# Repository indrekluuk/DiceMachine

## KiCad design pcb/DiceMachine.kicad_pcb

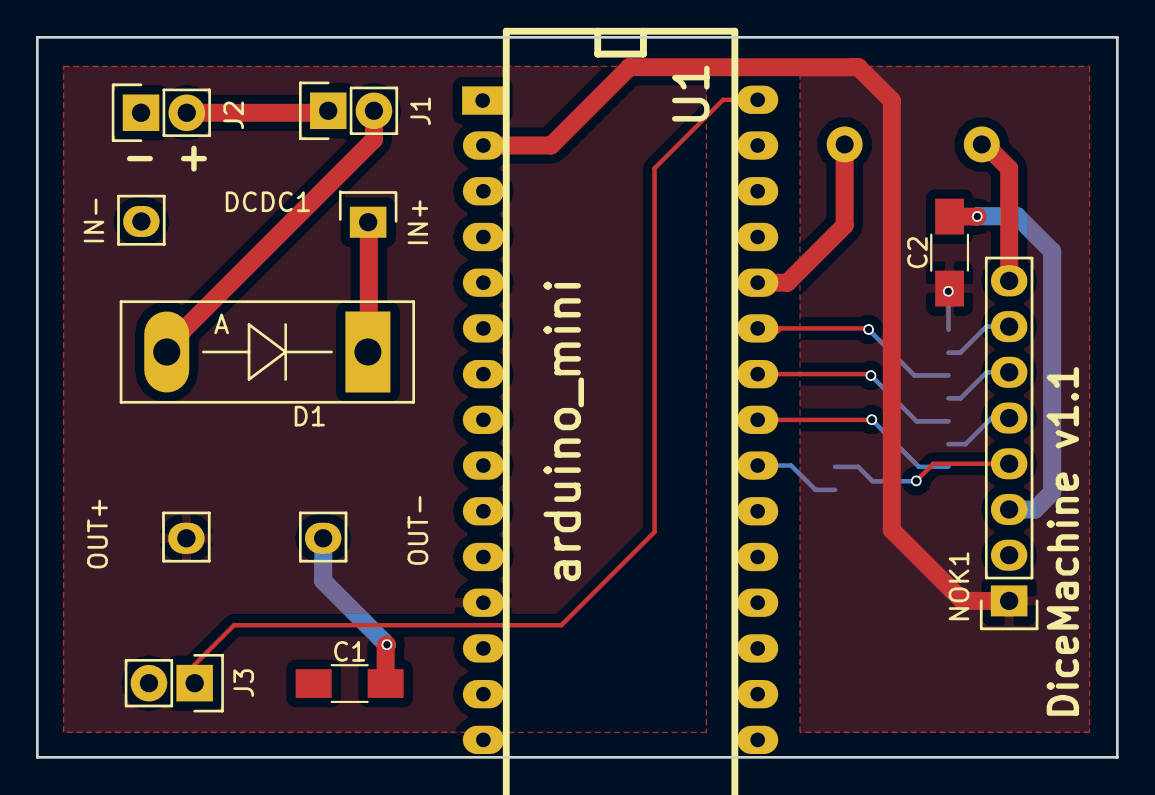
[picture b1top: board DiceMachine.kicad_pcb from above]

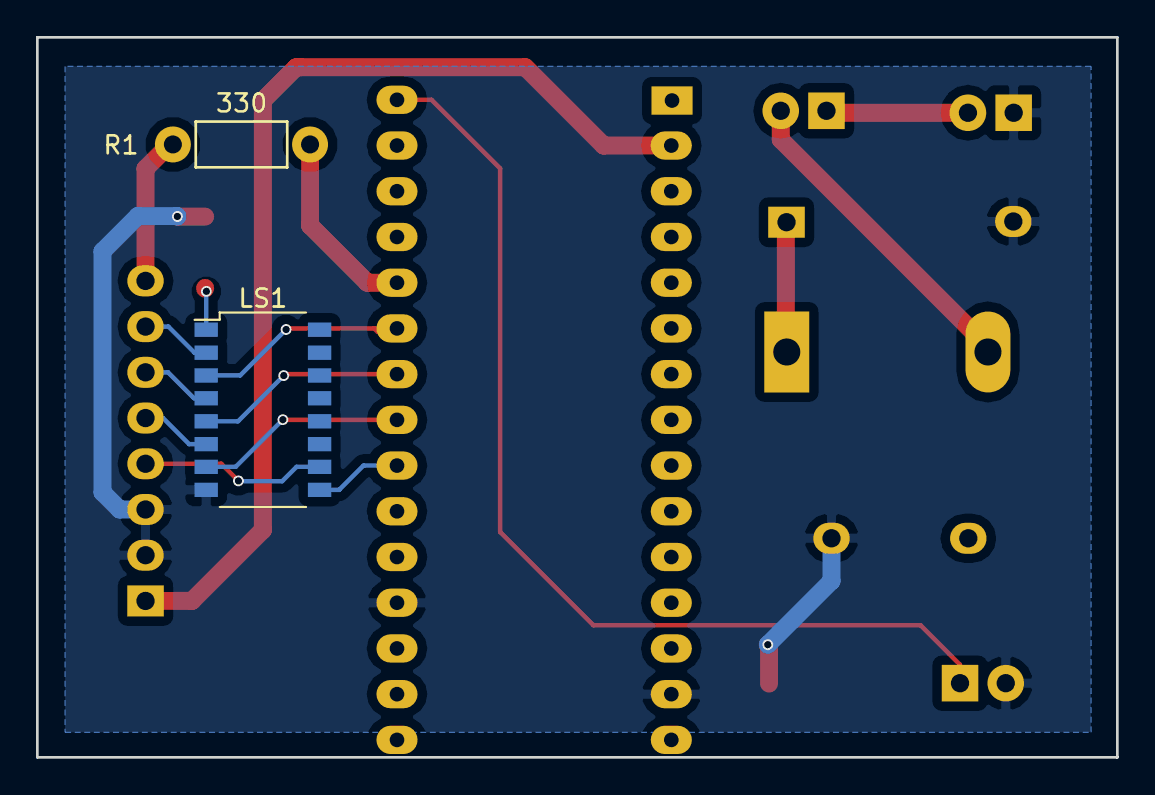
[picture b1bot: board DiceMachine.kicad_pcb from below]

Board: 2 copper layers, 60.0 x 40.0 mm, 11 parts (2 on the bottom side), 17 nets.

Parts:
C1, C2: C; C_1206_HandSoldering
D1: D; Diode_TO-247_Vertical
DCDC1: DcDcConverter; DcDc5VUp
J1, J2, J3: Conn_01x02; Pin_Header_Straight_1x02
LS1: LevelShifter_74HC4050D; SOP-16_4.4x10.4mm_Pitch1.27mm
NOK1: nok5110; Pin_Header_Straight_1x08
R1: 330; Resistor_Horizontal_RM7mm
U1: arduino_mini

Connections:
+3V3: C2.1, LS1.1, NOK1.1, U1.2
+5V: DCDC1.3, U1.12
GND: C1.2, C2.2, DCDC1.2, DCDC1.4, J2.1, J3.2, LS1.8, NOK1.2, NOK1.3, U1.14, U1.19
unnamed: D1.1, DCDC1.1
unnamed: D1.2, J1.2
unnamed: J1.1, J2.2
unnamed: J3.1, U1.30
unnamed: LS1.2, NOK1.7
unnamed: LS1.3, U1.25
unnamed: LS1.4, NOK1.6
unnamed: LS1.5, U1.24
unnamed: LS1.6, NOK1.5
unnamed: LS1.7, U1.23
unnamed: LS1.9, U1.22
unnamed: LS1.10, NOK1.4
unnamed: NOK1.8, R1.1
unnamed: R1.2, U1.26

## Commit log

2017-10-22 created PCB
2017-10-23 created PCB gerber files
2017-11-05 added level shifter to PCB
2017-11-26 re-generated PCB gerber files
2018-03-10 Removed IntelliJ project and addes stat project
2018-05-15 restored KiCad project
2018-05-15 Schema image
2018-05-15 Added STL files
2018-05-15 moved ino files to sub directories
2022-08-12 Updated dice to show statistics if button held down for 3 seconds.
